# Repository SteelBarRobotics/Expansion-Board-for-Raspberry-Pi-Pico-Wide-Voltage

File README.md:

# Expansion Board for Raspberry Pi Pico (Wide Voltage Version)

## Changes

- I2C pins changed to IO4 and IO5 for compatibility with default pins in arduino-pico and CircuitPython
- 4-28V voltage regulator added
- Mounting holes changed to M3 size
- Jumpers moved to front side to reduce chance of accidental shorts when unused
- Positioning posts under headers removed due to part availability

# PiicoDev® Expansion Board for Raspberry Pi Pico (Non-Recharging Version)
This is the repo for the Core Electronics [PiicoDev Expansion Board for Raspberry Pi Pico](https://core-electronics.com.au/catalog/product/view/sku/CE08670).

## License
This project is open source - please review the [LICENSE.md](LICENSE.md) file for further licensing information.

If you have any technical questions, or concerns about licensing, please contact technical support on the [Core Electronics forums](https://forum.core-electronics.com.au/).

*\"PiicoDev\" and the PiicoDev logo are trademarks of Core Electronics Pty Ltd.*

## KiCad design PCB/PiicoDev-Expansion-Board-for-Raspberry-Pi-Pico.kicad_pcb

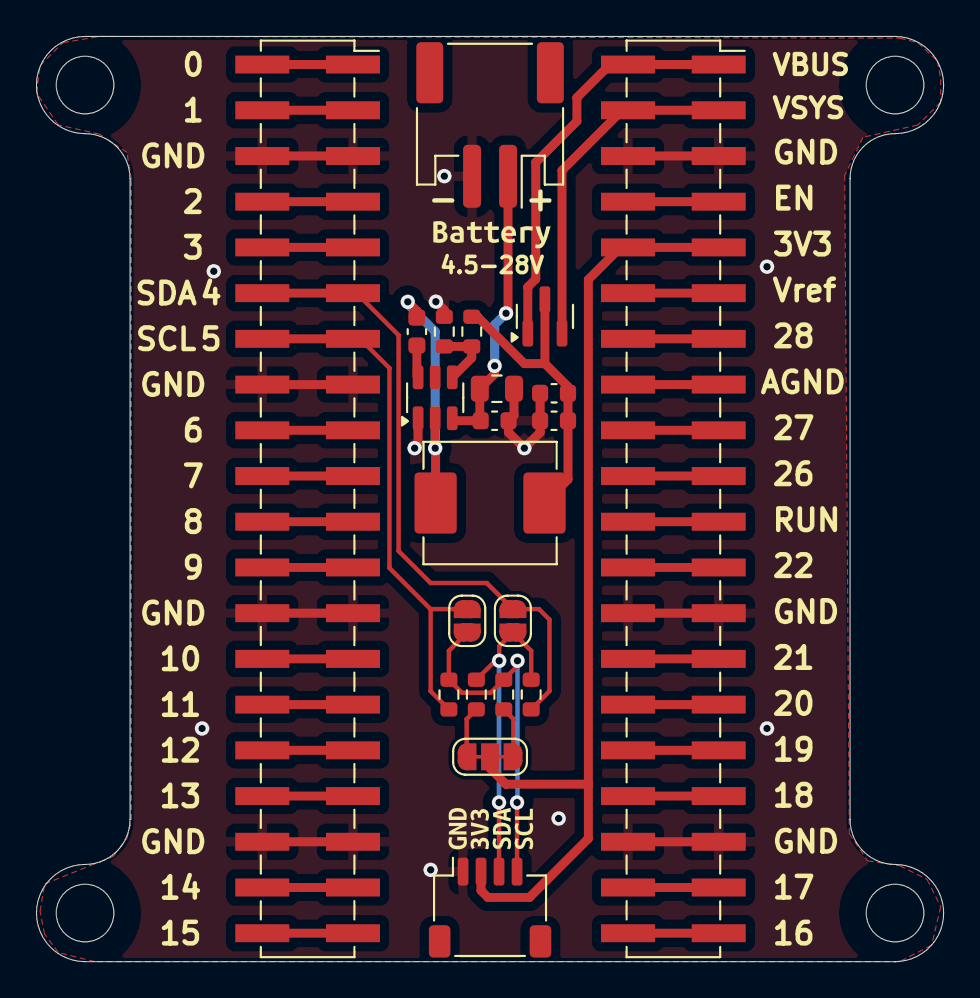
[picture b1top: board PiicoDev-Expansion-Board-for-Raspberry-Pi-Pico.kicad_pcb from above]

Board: 2 copper layers, 50.4 x 51.4 mm, 33 parts (3 on the bottom side), 43 nets.

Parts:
C1: 10uF; C_0805_2012Metric
C2, C3: 0.1uF; C_0603_1608Metric
C4, C5: 22uF; C_0603_1608Metric
H1, H2, H3, H4: MountingHole_3.2mm_M3
J1: PiicoDev; JST_SH_SM04B-SRSS-TB_1x04-1MP_P1.00mm_Horizontal
J2: JST PH; JST_PH_S2B-PH-SM4-TB_1x02-1MP_P2.00mm_Horizontal
J3, J4: PinSocket_2x20_P2.54mm_Vertical_SMD_With_Post
JP1, JP2: Bypass; SolderJumper-2_P1.3mm_Open_RoundedPad1.0x1.5mm
JP3: I2C; SolderJumper-3_P1.3mm_Closed_RoundedPad1.0x1.5mm
L1: 10uF; L_Abracon_ASPI-0630LR
Q1: MOSFET P-CH; SOT-23
R1: 100k; R_0603_1608Metric
R2: 13.3k; R_0603_1608Metric
R5, R6: 4k7; R_0603_1608Metric
R7, R8: 120R; R_0603_1608Metric
U1: TPS54302; SOT-23-6
kibuzzard-629D8D5D: G***; kibuzzard-629D8D5D
kibuzzard-629D8D6F: G***; kibuzzard-629D8D6F
kibuzzard-629D8D51: G***; kibuzzard-629D8D51
kibuzzard-629D8D64: G***; kibuzzard-629D8D64
kibuzzard-629D90AA: G***; kibuzzard-629D90AA
kibuzzard-629D909F: G***; kibuzzard-629D909F
kibuzzard-629D8642: G***; kibuzzard-629D8642
kibuzzard-629D9090: G***; kibuzzard-629D9090

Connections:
+3V3: J1.2, J4.9, J4.10, JP3.2 (C)
+5V: C4.1, C5.1, L1.2, Q1.3 (D), R1.1
/I2C0_SCL: J3.13, J3.14, JP2.2 (B), R8.1
/I2C0_SDA: J3.11, J3.12, JP1.1 (A), R7.1
/VSYS: J4.3, J4.4, Q1.2 (S)
GND: C1.2, C2.2, C4.2, C5.2, J1.1, J2.2, J3.5, J3.6, J3.15, J3.16, J3.25, J3.26, J3.35, J3.36, J4.5, J4.6, J4.25, J4.26, J4.35, J4.36, R2.2, U1.1 (GND)
unnamed: J4.7, J4.8
unnamed: J4.11, J4.12
unnamed: J3.1, J3.2
unnamed: J3.3, J3.4
unnamed: J3.7, J3.8
unnamed: J3.9, J3.10
unnamed: J3.17, J3.18
unnamed: J3.19, J3.20
unnamed: J3.21, J3.22
unnamed: J3.23, J3.24
unnamed: J3.27, J3.28
unnamed: J3.29, J3.30
unnamed: J3.31, J3.32
unnamed: J3.33, J3.34
unnamed: J3.37, J3.38
unnamed: J3.39, J3.40
unnamed: J4.39, J4.40
unnamed: J4.37, J4.38
unnamed: J4.33, J4.34
unnamed: J4.31, J4.32
unnamed: J4.29, J4.30
unnamed: J4.27, J4.28
unnamed: J4.23, J4.24
unnamed: J4.19, J4.20
unnamed: J4.17, J4.18
unnamed: J4.13, J4.14
unnamed: J4.21, J4.22
unnamed: J1.3, JP1.2 (B), R5.2, R7.2
unnamed: J1.4, JP2.1 (A), R6.2, R8.2
unnamed: J4.15, J4.16
unnamed: JP3.1 (A), R6.1
unnamed: JP3.3 (B), R5.1
unnamed: C3.2, U1.6 (BOOT)
unnamed: R1.2, R2.1, U1.4 (FB)
unnamed: C3.1, L1.1, U1.2 (SW)
VBAT: C1.1, C2.1, J2.1, U1.3 (VIN)
VBUS: J4.1, J4.2, Q1.1 (G)

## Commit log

2022-07-11 Add schematic.pdf
2022-08-10 Add image
2022-08-10 resize image
2024-08-19 Convert to KiCAD 8
2024-08-22 Wide voltage expansion board
2024-08-26 prototype production
2024-08-26 update schematic

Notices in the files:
PCB/PiicoDev-Expansion-Board-for-Raspberry-Pi-Pico.kicad_pcb:
CC BY-SA 4.0
